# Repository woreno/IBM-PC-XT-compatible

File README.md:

# IBM PC XT compatible (2022)
This is a IBM XT compatible built from scratch along 8 boards, 6 of them ISA 8-bit cards.

The design of the boards done here, is a bit personal. As other pcbs i do in-house, they are projected to be transfered with iron, drilled, then etched with iron perchlorate, using throught-hole chips, as many electronic and microcomputer hobbyists once did. To minimize errors on these manual procedures, circuits tracks and vias are made thicker. This project is about creating an IBM XT Compatible. This began in 2014, when i started to documenting home computer systems, like older and newer PCs, older systems like ZX Spectrum, MSX, Commodore, Amiga, Apple II, Macintosh, home and portable Sega, Nintendo and Sony entretainment systems, mainly for coding emulators. The IBM PC XT, was the second architecture to fully take notes after the ZX Spectrum.
In 2021, after manually designing and building an Apple 2 compatible computer and an Adlib card, i ask my self "it would be possible to build a bigger system like an IBM PC XT compatible using the same methods and tools???" (it seemed a big task by then). When i began, i wanted to be 8086 compatible, but the 16-bit bus and 16-bit memory organization logic, would make it impossible to fit in the maximum dimensions allowed by my own tools (A4 copper sheets), further the capacitance and thus distortion would be more pronounced on circuits.
Most components on IBM PC XT are Intel, DRAM, ROM ICs. Some control, demuxes and muxes, buffers, latches, and other glue logic is done using 74 series.

**BIOS**

* The BIOS is compiled with TASM using DOSBOX. 
* The BIOS was written from scratch except the INT10h (video services). The computer started without a videocard; first i built and relied on a ISA-card that displayed 4 seven-segment digits and 8 leds. Being the only way of displaying information from the computer, this board was very important, so after being built manually i tested rigorously the I/O with an ISA raiser, flipping buttons and multimeter, then, installing it on a Pentium PC and C Code. The BIOS has slowly developed step by step using this display board, so there's code everywhere that makes I/O to this board (including step and errors). After, i built the insane CGA card. At the first it used a primitive INT10h without a VBLANK wait (so a lot of white rain when printing), and at the end, since i was a bit exausted, i prefered to copy the original IBM PC XT INT10h code for having full compatiblity.
* After building the IDE/RTC card i had problems booting DOS. I had to CRC at each block at INT13h and do a comparasion with the groundtruth in another PC. So i end up to include also Single-Step and Breakpoint features, and debugging code traces at INT13h that can be activated by code. 
* The BIOS has a CGA welcome screen (compacted with RLE) and digitilized voices for digits (compacted with DeltaMod) these resources are glued and placed at 0xFB900. At the beggining at 0xF8000 there is the CRC and signature, and pointers to the previous resources. Theres a jump at 0xFFFF0 to the begining of the code. The voices were intended for announcing the time (with the RTC board) after POST, but at the end i decided to no call the feature, because it was too fancy.
* In the last revision of this computer, i added a switch to allow the PROMs to be written, and the BIOS can be updated via serial port, wifi or diskettes, so FAT code has added. Wifi was planned to added to the Paralllel/Serial/Joystick board, by adding a ESP8266 as the serial port (but i didn't finish this part); Wifi settings are stored in RTC memory along other BIOS settings. The make script composes a package to that goal.

**References**.
  * The Indispensable PC Hardware Book - Hans Peter Messmer; 1994
  * Digital Systems Project / Projecto de Sistemas Digitais (ISEL) - Victor Pimenta Rodrigues, Mário Seia de Araujo; 1988 (3th edition 2001)
  * IBM PC XT Technical Reference; 1983
  * Electrónica AC/DC/Analise circuitos - Santos, Guimarães e Oliveira, SA. Porto; 1980s
  * Interfacing to the IBM Personal Computer; Lewis C. Eggebrecht; 1983
  * Vintage Computer Federation (VCF)
  * GALBlast by Manfred Winterhoff
  * AT2XT Keyboard Adapter by Charles Guzis
  * XT-IDE by Charles Guzis, Vintage Computer Federation member (VCF)
  * HelpPC Reference Library by David Jurgens
  * Ben Eater's EEPROM arduino programmer
  * Dr Dobbs journal delta modulation
  * Every datasheet you can think of.

**Thanks to people i actually e-mailed them...**
  - CFG register will set the GALs scheme? Manfred Winterhoff, the author of GALBlast project
  - Can HTC lag on XT-IDE? Charles Guzis, the author of XT-IDE, XT2PS2 project
  - Whats the use of this diode on Adlib? the author of an Adlib, Sergey Malinov

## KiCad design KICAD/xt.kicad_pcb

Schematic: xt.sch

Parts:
C1: 5-30p; standard_2pins_half
C2, C4, C7, C9: 47p; standard_2pins_half
C3: .047; standard_2pins_half
C53: .01; standard_2pins_half
J1: IRQ8-15-Set; PinSocket_1x07_P2.54mm_Vertical
J9: xt_keyb_con; Conector1x5_Oval
P3: xt_speaker_con; Conector1x5_Oval
R1, R2: 510; standard_2pins
R3, R8, R9, R11, R12, R13, R17, R18, R19, R21, R22, R23, R24: R; standard_2pins
R4, R7: R
R4N_1, R4N_2, R4N_3, R4N_4: 30; standard_2pins
R5: 470; standard_2pins
R6: 33; standard_2pins
R15, R16: 4.7K; standard_2pins
R25: 8.2K; standard_2pins
RN1, RN2, RN3: 4.7K; R_Array_SIP9
RN4, RN5: 4.7K; R_Array_SIP10
RN4_0: 30; standard_2pins
SW1: SW_DIP_x08; Conector2x8_Oval
SW2: SW_DIP_x01
TD1: delay DS1000-100; standard_DIP_14OvalPins
U1: i8284_clockgen; standard_DIP_18pins_thin_body
U2, U9, U15: 74LS245; standard_DIP_20pins_thin_body
U3: i8088-CPU; standard_DIP_40pins_doubleBody_thinpins
U4, U19: PPROM_28C65_256; standard_DIP_28pins_thin_doubleBody
U5, U7: 74LS373; standard_DIP_20pins_thin_body
U6, U12, U14, U16, U17, U41: 74LS244; standard_DIP_20pins_thin_body
U8: 8288_busctrl; standard_DIP_20pins_thin_body
U10: 74LS670; standard_DIP_16OvalPins
U11: XD2ADDR-DMA; standard_DIP_20pins_thin_body
U13: 74LS243; standard_DIP_14OvalPins
U18: i8087-NPU; standard_DIP_40pins_doubleBody_thinpins
U20: ISA8-Edge; Conector2x31_Oval_0.65_rightangle
U21: 74LS175_separado; standard_DIP_16OvalPins
U22, U71, U220: 74LS04; standard_DIP_14OvalPins
U23: 74LS27; standard_DIP_14OvalPins
U24, U74: 74LS00; standard_DIP_14OvalPins
U25: i8259-PIC0; standard_DIP_28pins_thin_doubleBody
U26: 8255-PPI; standard_DIP_40pins_doubleBody_thinpins
U27: 74LS322; standard_DIP_20pins_thin_body
U28: i8254-PIT; standard_DIP_24pins_thin_doubleBody
U29, U57: 74LS20; standard_DIP_14OvalPins
U30: flipSwitch; mini_flipswitch2.54
U31: 74_175; standard_DIP_16OvalPins
U32, U38: manel-xt-pwer; manel-xt-power
U34: 8237-DMAC; standard_DIP_40pins_doubleBody_thinpins
U35, U36, U69: 74S00; standard_DIP_14OvalPins
U37: i8259-PIC1; standard_DIP_28pins_thin_doubleBody
U39, U40, U84: 74LS158; standard_DIP_16OvalPins
U42, U43: 74LS138; standard_DIP_16OvalPins
U44: flipSwitch
U55: 74S08; standard_DIP_14OvalPins
U56: 74S138; standard_DIP_16OvalPins
U58, U90: 74LS32; standard_DIP_14OvalPins
U68: 7407; standard_DIP_14OvalPins
U70: 74S74; standard_DIP_14OvalPins
U72: 74LS10; standard_DIP_14OvalPins
U73, U78, U86: 74LS74; standard_DIP_14OvalPins
U85: 75477_dual_peripheral_drvs; standard_DIP_8pins
U87: 74LS08; standard_DIP_14OvalPins
U89: 74S04; standard_DIP_14OvalPins
U100: xt-ram-exp; Conector2x25_Oval_0.65_rightangle
Y1: Crystal; standard_2pins

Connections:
/5V: C3.1, C4.1, J9.5 (VCC), P3.4 (VCC), R3.1, R4.1, R7.1, R8.2, R9.2, R11.1, R12.2, R13.2, R15.1, R16.2, R17.1, R18.1, R19.1, R21.2, R22.2, R23.1, R24.2, R25.2, RN1.1 (common), RN2.1 (common), RN3.1 (common), RN5.1 (common), TD1.14 (VCC), U1.18 (VCC), U2.20 (VCC), U3.40 (VCC), U4.28 (VCC), U5.20 (VCC), U6.20 (VCC), U7.20 (VCC), U8.20 (VCC), U9.20 (VCC), U10.16 (VCC), U11.20 (VCC), U12.20 (VCC), U13.14 (VCC), U14.20 (VCC), U15.20 (VCC), U16.20 (VCC), U17.20 (VCC), U18.40 (VCC), U19.28 (VCC), U20.3 (+5V), U20.29 (+5V), U21.16 (VCC), U22.14 (VCC), U23.14 (VCC), U24.14 (VCC), U25.28 (VCC), U26.26 (VCC), U27.20 (VCC), U28.11 (GATE0), U28.14 (GATE1), U28.24 (VCC), U29.14 (VCC), U31.16 (VCC), U32.3 (+5V), U32.4 (+5V), U34.5 (PIN5), U34.31 (VCC), U35.14 (VCC), U36.14 (VCC), U37.28 (VCC), U38.3 (+5V), U38.4 (+5V), U39.16 (VCC), U40.16 (VCC), U41.20 (VCC), U42.16 (VCC), U43.16 (VCC), U55.14 (VCC), U56.16 (VCC), U57.14 (VCC), U58.14 (VCC), U68.14 (VCC), U69.14 (VCC), U70.14 (VCC), U71.14 (VCC), U72.14 (VCC), U73.14 (VCC), U74.14 (VCC), U78.14 (VCC), U84.16 (VCC), U85.1 (S), U85.5 (CLAMP), U85.8 (VCC), U86.14 (VCC), U87.14 (VCC), U89.14 (VCC), U90.14 (VCC), U220.14 (VCC); also elsewhere on the board
/12V: U32.1 (+12V), U38.1 (+12V)
/+12V: U20.23 (IRQ5)
/-5V: U20.27 (TC), U32.5 (-5V), U38.5 (-5V)
/-12V: U20.25 (IRQ3), U32.2 (-12V), U38.2 (-12V)
/A0: U5.9 (O3), U12.18 (O0a), U17.11 (I0b), U20.62 (A0)
/A1: U5.12 (O4), U12.3 (O3b), U17.8 (I3a), U20.61 (A1)
/A2: U5.15 (O5), U12.16 (O1a), U17.13 (I1b), U20.60 (A2)
/A3: U5.6 (O2), U12.5 (O2b), U17.6 (I2a), U20.59 (A3)
/A4: U5.5 (O1), U12.14 (O2a), U17.15 (I2b), U20.58 (A4)
/A5: U5.16 (O6), U12.7 (O1b), U17.4 (I1a), U20.57 (A5)
/A6: U5.19 (O7), U12.9 (O0b), U17.2 (I0a), U20.56 (A6)
/A7: U5.2 (O0), U12.12 (O3a), U17.17 (I3b), U20.55 (A7)
/A8: U6.18 (O0a), U11.2 (O0), U16.15 (I2b), U20.54 (A8)
/A9: U6.16 (O1a), U11.5 (O1), U16.6 (I2a), U20.53 (A9)
/A10: U6.14 (O2a), U11.6 (O2), U16.17 (I3b), U20.52 (A10)
/A11: U6.12 (O3a), U11.9 (O3), U16.2 (I0a), U20.51 (A11)
/A12: U7.12 (O4), U11.12 (O4), U16.4 (I1a), U20.50 (A12)
/A13: U7.9 (O3), U11.15 (O5), U14.11 (I0b), U20.49 (A13)
/A14: U7.15 (O5), U11.16 (O6), U14.8 (I3a), U20.48 (A14)
/A15: U7.6 (O2), U11.19 (O7), U14.13 (I1b), U20.47 (A15)
/A16: U7.16 (O6), U10.10 (Q1), U14.6 (I2a), U20.46 (A16), U36.10
/A17: U7.5 (O1), U10.9 (Q2), U14.15 (I2b), U20.45 (A17), U35.4
/A18: U7.2 (O0), U10.7 (Q3), U14.4 (I1a), U20.44 (A18), U35.1, U35.2, U36.4
/A19: U7.19 (O7), U10.6 (Q4), U14.17 (I3b), U20.43 (A19), U35.10, U36.1, U36.2, U36.9
/AA8: U3.8 (A8), U6.2 (I0a), U18.8 (AD8)
/AA9: U3.7 (A9), U6.4 (I1a), U18.7 (AD9)
/AA10: U3.6 (A10), U6.6 (I2a), U18.6 (AD10)
/AA11: U3.5 (A11), U6.8 (I3a), U18.5 (AD11)
/AA12: U3.4 (A12), U7.13 (D4), U18.4 (AD12)
/AA13: U3.3 (A13), U7.8 (D3), U18.3 (AD13)
/AA14: U3.2 (A14), U7.14 (D5), U18.2 (AD14)
/AA15: U3.39 (A15), U7.7 (D2), U18.39 (AD15)
/AA16: U3.38 (A16.S3), U7.17 (D6), U18.38 (A16.S3)
/AA17: U3.37 (A17.S5), U7.4 (D1), U18.37 (A17.S4)
/AA18: U3.36 (A18.S6), U7.3 (D0), U18.36 (A18.S5)
/AA19: U3.35 (A19.S4), U7.18 (D7), U18.35 (A19.S6)
/AD0: U2.2 (A0), U3.16 (AD0), U5.8 (D3), U18.16 (AD0)
/AD1: U2.3 (A1), U3.15 (AD1), U5.13 (D4), U18.15 (AD1)
/AD2: U2.4 (A2), U3.14 (AD2), U5.14 (D5), U18.14 (AD2)
/AD3: U2.5 (A3), U3.13 (AD3), U5.7 (D2), U18.13 (AD3)
/AD4: U2.6 (A4), U3.12 (AD4), U5.4 (D1), U18.12 (AD4)
/AD5: U2.7 (A5), U3.11 (AD5), U5.17 (D6), U18.11 (AD5)
/AD6: U2.8 (A6), U3.10 (AD6), U5.18 (D7), U18.10 (AD6)
/AD7: U2.9 (A7), U3.9 (AD7), U5.3 (D0), U18.9 (AD7)
/ADDRSEL: TD1.3 (60NS), U39.1 (S), U40.1 (S), U84.1 (S)
/ADSTB: U11.11 (LE), U34.8 (ADSTB)
/AEN: U16.9 (O0b), U20.42 (AEN)
/AENBOARD: U5.1 (OE), U6.1 (OEa), U7.1 (OE), U8.6 (~AEN), U15.19 (CE), U16.11 (I0b), U17.1 (OEa), U17.19 (OEb), U31.2 (Q0), U31.5 (D1), U72.5, U74.4
/ALE: U5.11 (LE), U7.11 (LE), U8.5 (ALE), U20.4 (IRQ2/9)
/BA0: RN4.2 (R1), RN5.2 (R1), U39.4 (Za), U100.33 (~CAS0)
/BA1: RN4.3 (R2), RN5.3 (R2), U40.4 (Za), U100.32 (~RAS1)
/BA2: RN4.4 (R3), RN5.4 (R3), U39.7 (Zb), U100.31 (~CAS1)
/BA3: RN4.5 (R4), RN5.5 (R4), U40.7 (Zb), U100.30 (~RAS2)
/BA4: RN4.6 (R5), RN5.6 (R5), U39.9 (Zd), U100.29 (~CAS2)
/BA5: RN4.7 (R6), RN5.7 (R6), U40.9 (Zd), U100.28 (~RAS3)
/BA6: RN4.8 (R7), RN5.8 (R7), U39.12 (Zc), U100.27 (~CAS3)
/BA7: RN4.9 (R8), RN5.9 (R8), U40.12 (Zc), U100.26
/CLK: U16.7 (O1b), U20.12 (~MEMR), U31.9 (Cp), U89.9
/CLK88: U1.8 (CLK), U3.19 (CLK), U8.2 (CLK), U16.13 (I1b), U18.19 (CLK), U89.1
/CPU_GT0: RN1.2 (R1), U3.30 (HLDA.~RQ~/~GT1), U3.31 (HOLD.~RQ~/~GTO), U18.31 (~RQ/GTO)
/CPU_INT: U3.18 (INT), U25.17 (INT)
/CPU_NMI: U3.17 (NMI), U87.8
/D0: U2.18 (B0), U9.2 (A0), U15.2 (A0), U20.40 (D0)
/D1: U2.17 (B1), U9.3 (A1), U15.3 (A1), U20.39 (D1)
/D2: U2.16 (B2), U9.4 (A2), U15.4 (A2), U20.38 (D2)
/D3: U2.15 (B3), U9.5 (A3), U15.5 (A3), U20.37 (D3)
/D4: U2.14 (B4), U9.6 (A4), U15.6 (A4), U20.36 (D4)
/D5: U2.13 (B5), U9.7 (A5), U15.7 (A5), U20.35 (D5)
/D6: U2.12 (B6), U9.8 (A6), U15.8 (A6), U20.34 (D6)
/D7: U2.11 (B7), U9.9 (A7), U15.9 (A7), U20.33 (D7)
/DACK0: U56.4 (E1), U69.13, U220.4
/DATABUS_DIR: U2.1 (A->B), U8.4 (DT/~R)
/DATABUS_EN: U2.19 (CE), U22.12
/DBLCLK: U34.12 (CLK), U74.8
/DRAM_MODHI: U14.3 (O3b), U42.2 (A1), U43.6 (E3), U56.2 (A1)
/DRAM_MODLO: U36.11, U42.1 (A0), U56.1 (A0)
/DREQ0: U34.19 (DREQ0), U73.9 (Q)
/DREQ1: U20.14 (~IOR), U34.18 (DREQ1)
/DREQ2: U20.26 (~DACK2), U34.17 (DREQ2)
/DREQ3: U20.16 (DRQ3), U34.16 (DREQ3)
/ENRAMPCK: U26.22 (PB4)
/HOLDA: U31.4 (D0), U34.7 (HLDA), U73.5 (Q)
/HRQDMA: U29.5, U34.10 (HRQ), U73.1 (~R)
/IOCHRDY: R23.2, U20.41 (IO_READY), U78.10 (~S)
/IRQ0: U25.18 (IR0), U28.10 (OUT0)
/IRQ1: U25.19 (IR1), U27.1 (G), U70.5 (Q)
/IRQ2: U25.20 (IR2), U37.17 (INT)
/IRQ3: U20.7 (-12V), U25.21 (IR3)
/IRQ4: U20.8 (UNUSED), U25.22 (IR4)
/IRQ5: U20.9 (+12V), U25.23 (IR5)
/IRQ6: U20.10 (GND), U25.24 (IR6)
/IRQ7: U20.11 (~MEMW), U25.25 (IR7)
/IRQ8: J1.1, U37.18 (IR0)
/IRQ9: U20.28 (ALE), U37.19 (IR1)
/IRQ10: J1.2, U37.20 (IR2)
/IRQ11: J1.3, U37.21 (IR3)
/IRQ12: J1.4, U37.22 (IR4)
/IRQ13: J1.5, U37.23 (IR5)
/IRQ14: J1.6, U37.24 (IR6)
/IRQ15: J1.7, U37.25 (IR7)
/KBDCLK: C2.2, J9.1 (KBDCLK), R18.2, U21.4 (D0), U68.6
/KBDCLK2: U21.6 (~Q1), U27.11 (Clk), U70.3 (C)
/KBDDATA: C7.2, J9.2 (KBDDATA), R17.2, U27.17 (D1), U68.8
/MA8: RN4.10 (R9), RN5.10 (R9), U84.4 (Za), U100.25 (5V)
/MD0: U9.11 (B7), U100.3 (A2)
/MD1: U9.12 (B6), U100.2 (A1)
/MD2: U9.13 (B5), U100.1 (A0)
/MD3: U9.14 (B4), U100.50 (D0)
/MD4: U9.15 (B3), U100.49 (D1)
/MD5: U9.16 (B2), U100.48 (D2)
/MD6: U9.17 (B1), U100.46 (D4)
/MD7: U9.18 (B0), U100.47 (D3)
/NPU_INT: U18.32 (INT), U69.9
/NP_INSTALLED: RN3.3 (R2), SW1.2, U41.4 (I1a)
/OPTION1: RN3.2 (R1), SW1.1, U41.2 (I0a)
/OSC: U1.12 (OSC), U20.2 (RESET)
/PCLK: U1.2 (PCLK), U21.9 (CLK)
/PIC_CAS0: U25.12 (CAS0), U37.12 (CAS0)
/PIC_CAS1: U25.13 (CAS1), U37.13 (CAS1)
/PIC_CAS2: U25.15 (CAS2), U37.15 (CAS2)
/PIT_T1_OUT: U28.13 (OUT1), U73.11 (C), U100.6 (A5), U100.45 (D5)
/PIT_T2_OUT: U28.17 (OUT2), U87.13, U100.8 (A7), U100.43 (D7)
/PLANARRAM0: RN3.4 (R3), SW1.3, U41.6 (I2a)
/PLANARRAM1: RN3.5 (R4), SW1.4, U41.8 (I3a)
/PPI_JPR4: RN3.9 (R8), SW1.8, U26.17 (PC3), U41.12 (O3a)
/PPI_JPR5: RN3.8 (R7), SW1.7, U26.16 (PC2), U41.14 (O2a)
/PPI_JPR6: RN3.7 (R6), SW1.6, U26.15 (PC1), U41.16 (O1a)
/PPI_JPR7: RN3.6 (R5), SW1.5, U26.14 (PC0), U41.18 (O0a)
/PPI_PA0: U26.4 (PA0), U27.13 (H/Qh)
/PPI_PA1: U26.3 (PA1), U27.7 (G/Qg)
/PPI_PA2: U26.2 (PA2), U27.14 (F/Qf)
/PPI_PA3: U26.1 (PA3), U27.6 (E/Qe)
/PPI_PA4: U26.40 (PA4), U27.15 (D/Qd)
/PPI_PA5: U26.39 (PA5), U27.5 (C/Qc)
/PPI_PA6: U26.38 (PA6), U27.16 (B/Qb)
/PPI_PA7: U26.37 (PA7), U27.4 (A/Qa)
/PPI_PB3: R25.1, U26.21 (PB3), U41.1 (OEa), U100.11, U100.40, U220.1
/PPI_PB5: U26.23 (PB5), U89.13
/PPI_PB6: U26.24 (PB6), U68.5
/PPI_PB7: U26.25 (PB7), U27.8 (OE), U89.5
/PPI_PC4: U26.13 (PC4)
/PPI_PC5: U26.12 (PC5)
/PPI_PC6: U26.11 (PC6), U72.11, U74.2, U74.11
/PULLUP1: RN2.8 (R7), U18.33 (~RQ/GT1), U18.34 (~BHE/~S7)
/PWERGOOD: U1.11 (~RES)
/QS0: U3.25 (QS0.ALE), U18.25 (QS0)
/QS1: U3.24 (QS1.~INTA), U18.24 (QS1)
/RAS: TD1.1 (IN), U56.6 (E3), U69.6, U69.12
/RDYTODMA: U34.6 (READY), U87.3
/READY: U1.5 (READY), U3.22 (RDY), U18.22 (RDY)
/RESET: U1.10 (RESET), U3.21 (RST), U18.21 (RST), U26.35 (RESET), U34.13 (RESET), U89.3
/RESETDRV: U20.30 (OSC), U71.6
/RN1_6: RN1.3 (R2), U3.23 (~TEST), U18.23 (BUSY)
/RN1_7: RN1.8 (R7)
/RN1_9: RN1.9 (R8), U57.13
/ROMCS: U23.5, U24.8; also elsewhere on the board
/SPK: C53.1, R6.1, U85.6 (2Y)
/SPKRDATA: U26.19 (PB1), U87.12
/SS0: U3.34 (~SS0.HIGH)
/TIM2GATESPK: U26.18 (PB0), U28.16 (GATE2), U100.14 (GND), U100.37
/TIMER_CLK: U21.10 (Q2), U28.9 (CLK0), U28.15 (CLK1), U28.18 (CLK2), U100.13 (GND), U100.38 (~WR)
/T\C: U20.5 (-5V), U220.8
/X1: C1.2, R1.1, U1.17 (X1)
/X2: R2.1, U1.16 (X2), Y1.2
/XA0: U4.10 (A0), U10.14 (Wa), U12.2 (I0a), U17.9 (O0b), U19.10 (A0), U25.27 (A0), U26.9 (A0), U28.19 (A0), U34.32 (A0), U37.27 (A0), U39.2 (I0a)
/XA1: U4.9 (A1), U10.13 (Wb), U12.17 (I3b), U17.12 (O3a), U19.9 (A1), U26.8 (A1), U28.20 (A1), U34.33 (A1), U40.2 (I0a), U100.15 (GND), U100.36
/XA2: U4.8 (A2), U12.4 (I1a), U17.7 (O1b), U19.8 (A2), U34.34 (A2), U39.5 (I0b)
/XA3: U4.7 (A3), U12.15 (I2b), U17.14 (O2a), U19.7 (A3), U34.35 (A3), U40.5 (I0b)
/XA4: U4.6 (A4), U12.6 (I2a), U17.5 (O2b), U19.6 (A4), U34.37 (A4), U39.11 (I0d), U58.2, U58.4
/XA5: U4.5 (A5), U12.13 (I1b), U17.16 (O1a), U19.5 (A5), U34.38 (A5), U40.11 (I0d); also elsewhere on the board
/XA6: U4.4 (A6), U12.11 (I0b), U17.18 (O0a), U19.4 (A6), U34.39 (A6), U39.14 (I0c); also elsewhere on the board
/XA7: U4.3 (A7), U12.8 (I3a), U17.3 (O3b), U19.3 (A7), U34.40 (A7), U40.14 (I0c); also elsewhere on the board
/XA8: U4.25 (A8), U16.5 (O2b), U19.25 (A8), U40.3 (I1a), U44.3 (line2), U58.1; also elsewhere on the board
/XA9: U4.24 (A9), U16.14 (O2a), U19.24 (A9), U23.2, U39.6 (I1b); also elsewhere on the board
/XA10: U4.21 (A10), U16.3 (O3b), U19.21 (A10), U40.6 (I1b)
/XA11: U4.23 (A11), U16.18 (O0a), U19.23 (A11), U39.10 (I1d)
/XA12: U4.2 (A12), U16.16 (O1a), U19.2 (A12), U40.10 (I1d)
/XA13: U4.26 (A13), U14.9 (O0b), U19.26 (A13), U39.13 (I1c)
/XA14: U4.1 (A14), U14.12 (O3a), U19.1 (A14), U39.3 (I1a)
/XA15: U14.7 (O1b), U40.13 (I1c), U43.1 (A0)
/XA16: U14.14 (O2a), U43.2 (A1), U84.2 (I0a)
/XA17: U14.5 (O2b), U43.3 (A2), U84.3 (I1a)
/XA18: U14.16 (O1a), U24.1, U24.2; also elsewhere on the board
/XD0: U4.11 (D0), U10.15 (D1), U11.3 (D0), U15.18 (B0), U19.11 (D0), U25.11 (D0), U26.34 (D0), U28.8 (D0), U34.30 (D0), U37.11 (D0)
/XD1: U4.12 (D1), U10.1 (D2), U11.4 (D1), U15.17 (B1), U19.12 (D1), U25.10 (D1), U26.33 (D1), U28.7 (D1), U34.29 (D1), U37.10 (D1)
/XD2: U4.13 (D2), U10.2 (D3), U11.7 (D2), U15.16 (B2), U19.13 (D2), U25.9 (D2), U26.32 (D2), U28.6 (D2), U34.28 (D2), U37.9 (D2)
/XD3: U4.15 (D3), U10.3 (D4), U11.8 (D3), U15.15 (B3), U19.15 (D3), U25.8 (D3), U26.31 (D3), U28.5 (D3), U34.27 (D3), U37.8 (D3)
/XD4: U4.16 (D4), U11.13 (D4), U15.14 (B4), U19.16 (D4), U25.7 (D4), U26.30 (D4), U28.4 (D4), U34.26 (D4), U37.7 (D4)
/XD5: U4.17 (D5), U11.14 (D5), U15.13 (B5), U19.17 (D5), U25.6 (D5), U26.29 (D5), U28.3 (D5), U34.23 (D5), U37.6 (D5)
/XD6: U4.18 (D6), U11.17 (D6), U15.12 (B6), U19.18 (D6), U25.5 (D6), U26.28 (D6), U28.2 (D6), U34.22 (D6), U37.5 (D6)
/XD7: U4.19 (D7), U11.18 (D7), U15.11 (B7), U19.19 (D7), U25.4 (D7), U26.27 (D7), U28.1 (D7), U34.21 (D7), U37.4 (D7), U86.12 (D)
/XMEMR: U71.10, U72.4
/\eop: R19.2, U34.36 (~EOP), U220.9
/efi: U1.14 (EFI)
/~AEN: U8.15 (CEN), U31.3 (~Q0), U57.9; also elsewhere on the board
/~CAS: U42.5 (E2), U69.3
/~CAS0: U42.15 (O0), U100.20 (5V)
/~CAS1: U42.14 (O1), U100.21 (~5V)
/~CAS2: U42.13 (O2), U100.22 (~5V)
/~CAS3: U42.12 (O3), U100.23 (~5V)
/~DACK0: U16.12 (O3a), U20.13 (~IOW)
/~DACK0BRD: U16.8 (I3a), U24.4, U34.25 (~DACK0), U42.6 (E3), U72.3, U73.13 (~R), U78.12 (D), U220.3; also elsewhere on the board
/~DACK1: U20.15 (~DACK3), U34.24 (~DACK1)
/~DACK2: U10.4 (Rb), U20.6 (DRQ2), U34.14 (~DACK2)
/~DACK3: U10.5 (Ra), U20.17 (~DACK1), U34.15 (~DACK3)
/~DATABUS_EN: U8.16 (DEN), U22.13
/~DMACS: U34.11 (~CS), U90.13; also elsewhere on the board
/~DMAEN: U10.11 (~Er), U11.1 (OE), U12.1 (OEa), U12.19 (OEb), U13.1 (OEa), U13.13 (OEb), U74.6
/~DMAWAIT: U1.4 (RDY1), U31.6 (~Q1)
/~HDD_CS: R4.2, U23.9
/~INTA: RN2.6 (R5), U8.14 (~INTA), U24.13, U25.26 (~INTA), U37.26 (~INTA), U100.12 (GND), U100.39; also elsewhere on the board
/~IOCHK: R8.1, U20.32 (~IOCHK), U74.1
/~IOR: RN2.4 (R3), U8.13 (~IORC), U13.8 (B3), U20.18 (DRQ1)
/~IOW: RN2.2 (R1), U8.12 (~AIOWC), U13.10 (B1), U20.19 (~DACK0)
/~KBDRESET: C9.2, J9.3 (~KBDRESET), U21.1 (~MR), U31.1 (~Mr), U71.5, U86.13 (~R), U89.4
/~LOCK: U3.29 (~WR~.~LOCK), U29.1
/~MEMR: RN2.7 (R6), U8.7 (~MRDC), U13.11 (B0), U20.20 (CLK88), U57.12
/~MEMW: RN2.5 (R4), U8.8 (~AMWC), U13.9 (B2), U20.21 (IRQ7), U30.1 (line1)
/~MWTC: RN2.3 (R2), U8.9 (~MWTC), U57.10
/~PIC0CS: U25.1 (~CS); also elsewhere on the board
/~PIC1CS: U37.1 (~CS), U100.9 (A8), U100.42; also elsewhere on the board
/~PPICS: U26.6 (~CS), U58.6, U100.10, U100.41
/~RAMADDRSEL: U9.19 (CE), U24.6, U42.4 (E1), U56.5 (E2); also elsewhere on the board
/~RAS0: R4N_1.1, U100.16 (GND)
/~RAS1: R4N_2.1, U100.17
/~RAS2: R4N_3.1, U100.18
/~RAS3: R4N_4.1, U100.19 (5V)
/~RDY~\WAIT: U1.3 (~AEN1), U31.12 (D2), U78.9 (Q)
/~REFRESH_GATE: U55.1, U55.4, U55.10, U55.13, U69.11
/~ROMCS0: U4.20 (~CE), U4.22 (~OE), U24.9, U43.9 (O6); also elsewhere on the board
/~ROMCS1: U19.20 (~CE), U19.22 (~OE), U24.10, U43.7 (O7); also elsewhere on the board
/~ROMWR: U4.27 (~WE), U19.27 (~WE), U30.2 (short)
/~S0: U3.26 (~DEN.~S0), U8.19 (~S0), U18.26 (~S0), U29.4
/~S1: U3.27 (DT/~R~.~S1), U8.3 (~S1), U18.27 (~S1), U29.2
/~S2: U3.28 (IO/~M~.~S2), U8.18 (~S2), U18.28 (~S2)
/~TCCS: U28.21 (~CS); also elsewhere on the board
/~WE: RN4_0.1, U100.35
/~WRTDMAPGREG: U10.12 (~Ew), U58.8
/~WRTNMIREG: U58.11, U86.11 (C)
/~XIOR: RN1.7 (R6), U13.6 (A3), U23.1, U23.10, U23.11, U25.3 (~RD), U26.5 (~RD), U28.22 (~RD), U34.1 (~IOR), U37.3 (~RD), U72.13, U100.7 (A6), U100.44 (D6)
/~XIOW: RN1.5 (R4), U13.4 (A1), U25.2 (~WR), U26.36 (~WR), U28.23 (~WR), U34.2 (~IOW), U37.2 (~WR), U58.10, U58.12, U72.1, U90.12
/~XMEMR: RN1.4 (R3), U9.1 (A->B), U13.3 (A0), U34.3 (~MEMR), U43.5 (E2), U69.5, U71.11
/~XMEMW: RN1.6 (R5), U13.5 (A2), U22.1, U34.4 (~MEMW), U69.4
Earth: C2.1, C3.2, C4.2, C7.1, C9.1, C53.2, J9.4 (GND), P3.3 (GND), R1.2, R2.2, RN4.1 (common), SW1.13, SW1.14, SW1.15, SW1.16, SW2.1, TD1.7 (GND), U1.1 (CSYNC), U1.6 (RDY2), U1.9 (GND), U1.13 (F/~C), U1.15 (~ASYNC), U2.10 (GND), U3.1 (GND), U3.20 (GND), U3.33 (MIN/~MAX), U4.14 (GND), U5.10 (GND), U6.10 (GND), U7.10 (GND), U8.1 (Multibus), U8.10 (GND), U9.10 (GND), U10.8 (GND), U11.10 (GND), U12.10 (GND), U13.7 (GND), U14.1 (OEa), U14.10 (GND), U14.19 (OEb), U15.10 (GND), U16.1 (OEa), U16.10 (GND), U16.19 (OEb), U17.10 (GND), U18.1 (GND), U18.20 (GND), U19.14 (GND), U20.1 (GND), U20.22 (IRQ6), U20.31 (GND), U21.8 (GND), U22.7 (GND), U23.7 (GND), U24.7 (GND), U25.14 (GND), U26.7 (GND), U26.10 (PC7), U27.10 (GND), U28.12 (GND), U29.7 (GND), U31.8 (GND), U32.7 (GND), U32.8 (GND), U34.20 (GND), U35.7 (GND), U36.7 (GND), U37.14 (GND), U37.16 (~SP~/~EN), U38.7 (GND), U38.8 (GND), U39.8 (GND), U39.15 (E), U40.8 (GND), U40.15 (E), U41.10 (GND), U42.3 (A2), U42.8 (GND), U43.8 (GND), U55.7 (GND), U56.8 (GND), U57.7 (GND), U58.7 (GND), U68.7 (GND), U69.7 (GND), U70.7 (GND), U71.7 (GND), U72.7 (GND), U73.7 (GND), U74.7 (GND), U78.7 (GND), U84.8 (GND), U84.15 (E), U85.4 (GND), U86.7 (GND), U87.7 (GND), U89.7 (GND), U90.7 (GND), U220.7 (GND); also elsewhere on the board
unnamed: C1.1, Y1.1
unnamed: P3.1 (KEY), R6.2
unnamed: R3.2, U30.3 (line2)
unnamed: R4N_1.2, U55.3
unnamed: R4N_2.2, U55.11
unnamed: R4N_3.2, U55.6
unnamed: R4N_4.2, U55.8
unnamed: R5.1, U89.8
unnamed: R5.2, U74.9
unnamed: R9.1, U69.10
unnamed: R11.2, U27.2 (S/P), U27.3 (D0), U27.18 (SE), U27.19 (DS)
unnamed: R12.1, U72.9
unnamed: R13.1, U86.10 (~S)
unnamed: R15.2, U1.7 (~AEN2)
unnamed: R16.1, U25.16 (~SP~/~EN)
unnamed: R21.1, U26.20 (PB2)
unnamed: R22.1, U73.10 (~S), U73.12 (D)
unnamed: R24.1, U56.3 (A2)
unnamed: RN4_0.2, U22.4
unnamed: SW1.9, U68.10
unnamed: SW1.10, U68.12
unnamed: SW1.11, U68.4
unnamed: SW1.12, U68.2
unnamed: SW2.2, U69.8, U72.10
unnamed: TD1.5 (100NS), U69.1
unnamed: U15.1 (A->B), U23.6
unnamed: U21.2 (Q0), U21.5 (D1)
unnamed: U21.11 (~Q2), U21.12 (D2)
unnamed: U22.2, U22.3
unnamed: U22.5, U90.11
unnamed: U22.6, U90.10
unnamed 302: U23.4, U24.11; also elsewhere on the board
unnamed: U23.3, U23.12
unnamed: U23.13, U44.2 (short)
unnamed 305: U24.3, U43.4 (E1); also elsewhere on the board
unnamed 306: U24.5, U35.8; also elsewhere on the board
unnamed: U27.9 (Clr), U70.1 (~R), U89.6
unnamed: U27.12 (Qh), U70.2 (D)
unnamed: U29.6, U90.9
unnamed: U31.7 (Q1), U74.5
unnamed: U31.11 (~Q2), U78.13 (~R), U87.2
unnamed: U31.13 (D3), U71.2
unnamed: U31.15 (Q3), U73.2 (D)
unnamed 318: U58.13; also elsewhere on the board
unnamed 319: U58.9; also elsewhere on the board
unnamed 320: U58.5; also elsewhere on the board
unnamed: U35.9, U35.11
unnamed: U35.6, U35.12
unnamed: U35.3, U35.5, U35.13
unnamed: U36.3, U36.5
unnamed: U36.6, U36.12
unnamed: U36.8, U36.13
unnamed: U44.1 (line1), U58.3
unnamed: U55.2, U56.11 (O4)
unnamed: U55.5, U56.9 (O6)
unnamed: U55.9, U56.7 (O7)
unnamed: U55.12, U56.10 (O5)
unnamed: U57.8, U69.2
unnamed: U68.9, U70.4 (~S), U70.6 (~Q)
unnamed: U71.1, U90.8
unnamed: U72.2, U72.6
unnamed: U72.8, U87.10
unnamed: U72.12, U78.11 (C)
unnamed: U73.3 (C), U74.10, U89.2
unnamed: U73.4 (~S), U73.6 (~Q)
unnamed: U74.3, U74.12
unnamed: U74.13, U89.12
unnamed: U78.8 (~Q), U87.1
unnamed: U85.7 (2A), U87.11
unnamed: U86.9 (Q), U87.9
unnamed: U68.1, U68.3, U68.11, U68.13, U220.2
unnamed: U24.12, U220.12
unnamed: U23.8, U220.13

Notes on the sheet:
O gerador de clocks produz apartir de OSC CLK : 1/3 de OSC, 33% duty PCLK : 1/6 de OSC, 50% duty
OSC é gerado apartir dum oscilador cristal a 14.31818MHz
presa do endereço alto
~OE + S/~P=LO => parallel load data in: clock ascendente
este driver para 2 cargas era suposto além de levar o sinal de out2 para speaker, levar o sinal MOTORON para o recorder por 1A-1Y, (no PC original desde PB3, substituido)
aqui esta esquizita forma de comutar os jumpers se PB3=LO passa o transceiver 244 com a parte baixa dos jumpers e o inversor fica a HI, não fazendo diferença os jumpers da parte alta; se PB3=HI a parte baxa não passa e o inversor fica à terra, deixando passar os jumpers na parte alta (porque ligam 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
este PIP está a contar que vai ser programado para que as linhas PPI_A e PPI_C serem de leitura (IN), PPI_B serem de escrita (OUT)
desde cpu e controlador DMA se CPU em ESTADO PASSIVO ou HALT e não lock, e houver request DMA então proceder
um pedido dum canal DMA, desde controlador DMA
confirmação de cedência para o controlador DMA
para gerador clocks
e ativar controlador DMA
para READY no controlador DMA (sinal anologo a /IOCHRDY mas para o DMA)
para fachada com bus local
para controlador bus
para clock controlador DMA
pedido de atualização de memória (canal 0) apenas se não houver confirmação do mesmo ainda
esta delay line foi substuido por resistência em versões post.
divisor da frequência de PCLK resulta numa freq. de 1.193180MHz vai para todos os contadores do PIT
temporizador 1 vai para pedido DMA canal 0, atualização de memória
> (aos slots)
transceiver <<>> se em dma (A->B, ex. MEMR <- XMEMR) normalmente (B->A, ex. MEMR -> XMEMR) (se em dma o BUS CTRL tem de se afastar de MEMRx, IOWx, etc)
presa 4x4 bits; guarda as páginas para cada canal DMA; se a flag de acesso I/O "WRTDMAPGREG" escreve em A16:A19, a página respetiva ao número em XA0:1 vinda de XD0:4 se em DMA "~DMAEN~", a página é exposta em A16:19 (no bus sistema)
presa de 8 bits; prende a "parte meia" do endereço (configurada no DMA para o canal ativo), passada por XD0:7 com o sinal "ADSTB" pelo controlador de DMA; expõem o endereço A8:15 (no bus de sistema)
ativa o registo para escrever os MSBs do endereço de memória para cada canal
0xC0 apaga ou faz set para (na verdade como clk) ao ff que ativa/inibe todas as NMIs
para expansão bus
este ff, guarda em Q o inibidor da NMI
descodifica endereço base I/O 0h, 20h, 40h, 60h e ativa o respetivo chip DMA,INT,PIT,PPI ou 80h registo de página DMA para escrever MSBs altos, ou A0h o ff para inibir/permitir as NMI
desde NPU
erro dispositivo (IOCHK lógica positiva)
desde slots, o dispositiivo tem de a pushar a zero se erro (na notação original este sinal está sem traço)
desde PPI (jumpers)
desde PPI
Alimentação tb vai à parte para a placa de expansão
dados/endereço multiplexado: parte baixa AD0:7
multiplexa o endereço para o endereço linha ou coluna É IMPORTANTE que XA0:7 seja o endereço RAS, porque o DMA roda o endereço baixo XA0:7 para atualização de memória
fachada com bus CPU <-> bus sistema ----------------------------------------- * ALE (desde controlador de bus) prende o endereço multiplexado nas presas e expõem ao bus de sistema * AENBRD (desde GEN SINALS) deixa em alta impedância os transceivers e presas com o CPU, para separâ-lo do bus de siste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
transceiver de dados desde/para a memória
buffer >>

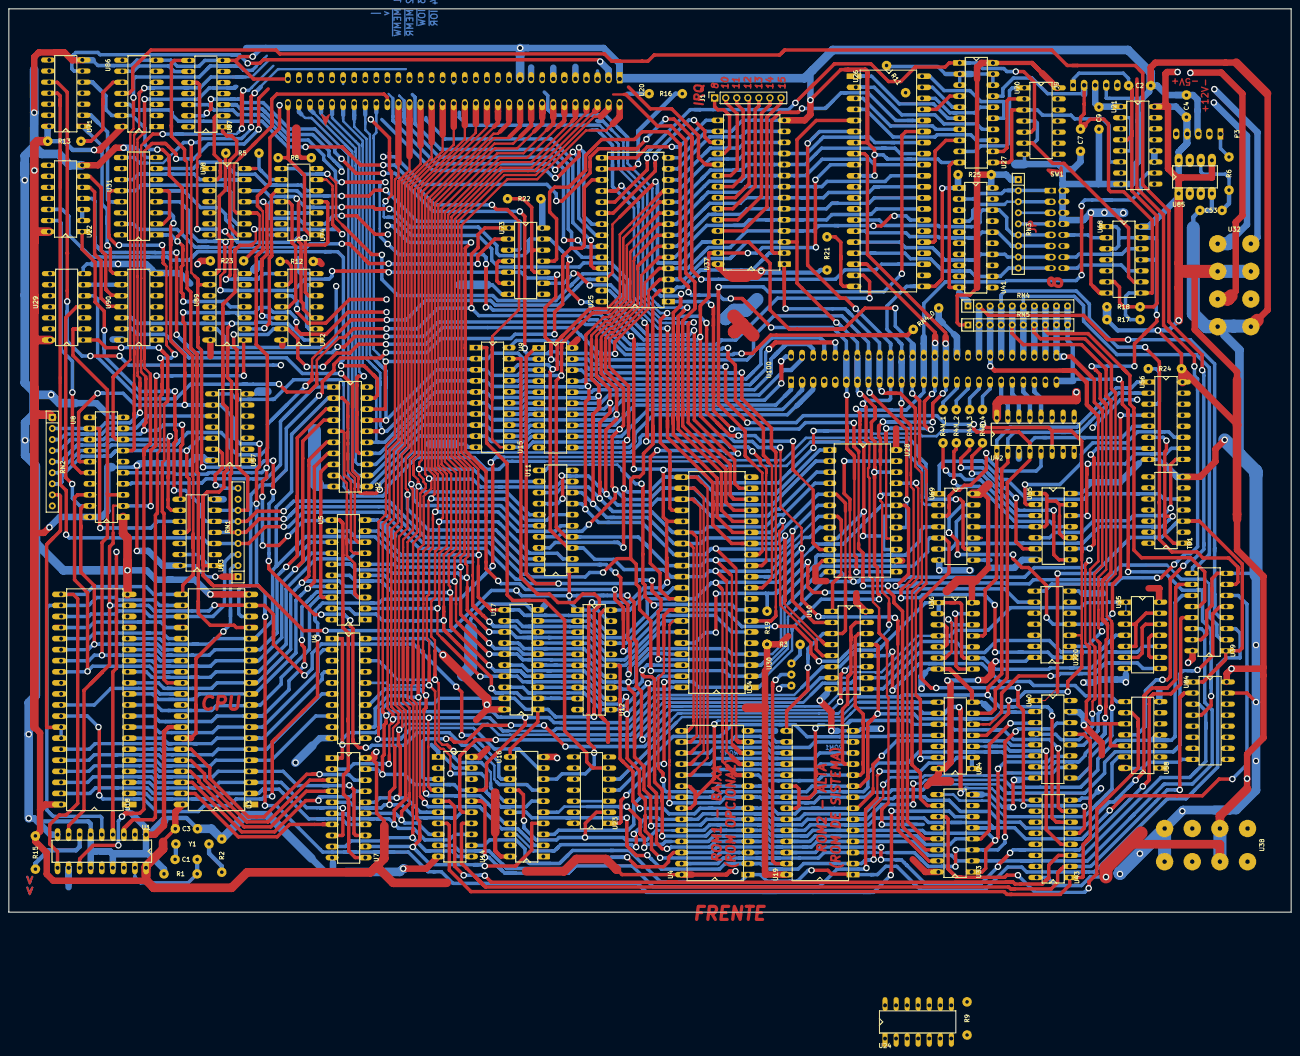
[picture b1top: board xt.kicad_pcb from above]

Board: 2 copper layers, 294.5 x 207.5 mm, 107 parts (0 on the bottom side), 307 nets.

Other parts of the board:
U24#2: 74LS00; standard_DIP_14OvalPins
U33: 74LS138; standard_DIP_16OvalPins

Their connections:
/5V: U24#2.14, U33.16; also elsewhere on the board
/ROMCS: U24#2.8; also elsewhere on the board
/XA5: U33.1; also elsewhere on the board
/XA6: U33.2; also elsewhere on the board
/XA7: U33.3; also elsewhere on the board
/XA8: U33.4; also elsewhere on the board
/XA9: U33.5; also elsewhere on the board
/XA18: U24#2.1, U24#2.2; also elsewhere on the board
/~AEN: U33.6; also elsewhere on the board
/~DACK0BRD: U24#2.4; also elsewhere on the board
/~DMACS: U33.15; also elsewhere on the board
/~INTA: U24#2.12, U24#2.13; also elsewhere on the board
/~PIC0CS: U33.14; also elsewhere on the board
/~PIC1CS: U33.10; also elsewhere on the board
/~RAMADDRSEL: U24#2.6; also elsewhere on the board
/~ROMCS0: U24#2.9; also elsewhere on the board
/~ROMCS1: U24#2.10; also elsewhere on the board
/~TCCS: U33.13; also elsewhere on the board
Earth: U24#2.7, U33.8; also elsewhere on the board
unnamed 302: U24#2.11; also elsewhere on the board
unnamed 305: U24#2.3; also elsewhere on the board
unnamed 306: U24#2.5; also elsewhere on the board
unnamed 318: U33.9; also elsewhere on the board
unnamed 319: U33.11; also elsewhere on the board
unnamed 320: U33.12; also elsewhere on the board
